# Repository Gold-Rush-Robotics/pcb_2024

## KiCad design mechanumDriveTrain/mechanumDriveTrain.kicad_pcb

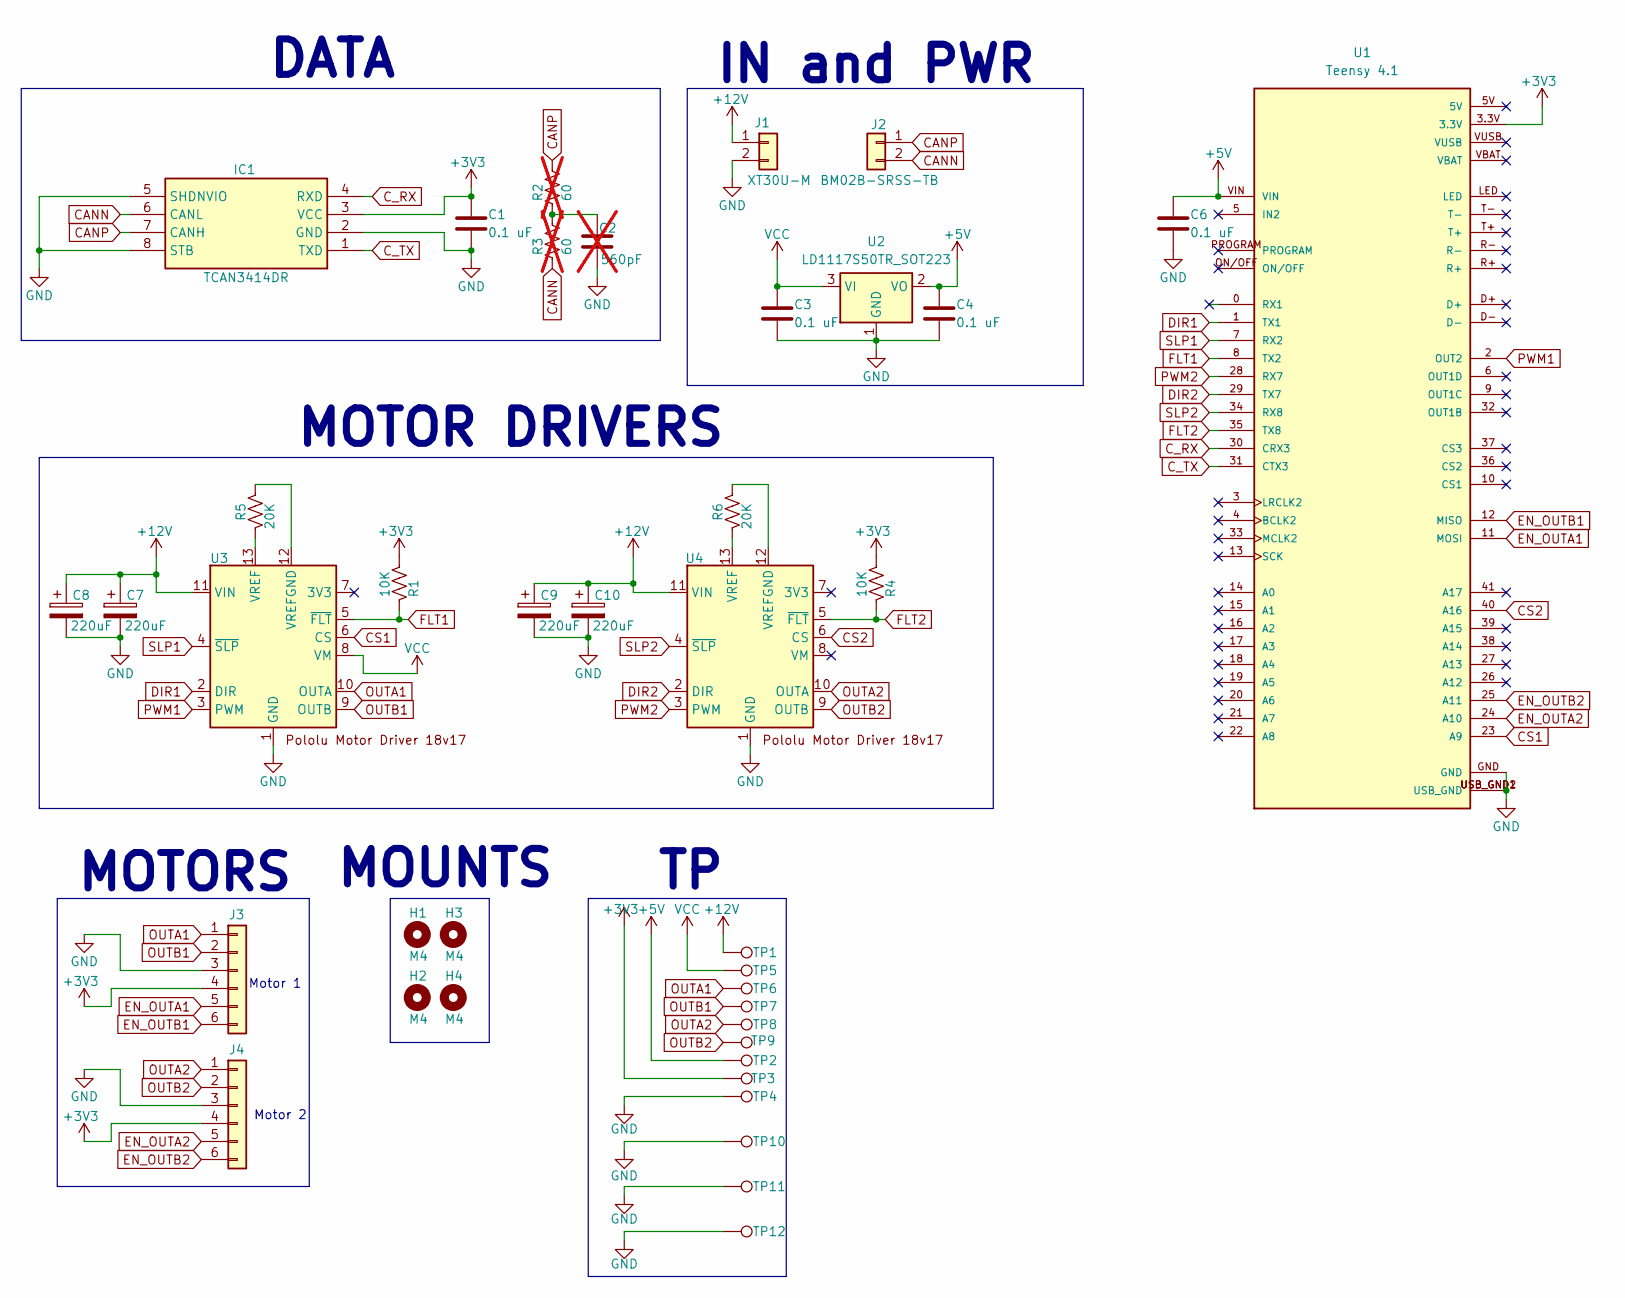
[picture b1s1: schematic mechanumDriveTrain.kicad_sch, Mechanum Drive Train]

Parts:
C1, C3, C4, C6: 0.1 uF; C_0805_2012Metric_Pad1.18x1.45mm_HandSolder
C2: 560pF; C_0805_2012Metric_Pad1.18x1.45mm_HandSolder; not fitted
C7, C8, C9, C10: 220uF; CP_Radial_D6.3mm_P2.50mm
H1, H2, H3, H4: M4; MountingHole_4.3mm_M4_DIN965
IC1: TCAN3414DR; SOIC-8_3.9x4.9mm_P1.27mm; Mouser Part Number 595-TCAN3414DR
J1: XT30U-M; AMASS_XT30U-M_1x02_P5.0mm_Vertical
J2: BM02B-SRSS-TB; JST_SH_BM02B-SRSS-TB_1x02-1MP_P1.00mm_Vertical
J3, J4: 5 pin dupont; PinHeader_1x06_P2.54mm_Vertical
R1, R4: 10K; R_0805_2012Metric_Pad1.20x1.40mm_HandSolder
R2, R3: 60; R_0805_2012Metric_Pad1.20x1.40mm_HandSolder; not fitted
R5, R6: 20K; R_Axial_DIN0207_L6.3mm_D2.5mm_P5.08mm_Vertical
TP1, TP2, TP3, TP4, TP5, TP6, TP7, TP8, TP9, TP10, TP11, TP12: TestPoint_Loop_D1.80mm_Drill1.0mm_Beaded
U1: Teensy 4.1; Teensy41; PARTREV 4.1
U2: LD1117S50TR_SOT223; SOT-223-3_TabPin2
U3, U4: Pololu_G2_Motor_Driver_18v17

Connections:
+3V3: C1.1, IC1.3 (VCC), J3.4, J4.4, R1.1, R4.1, TP3.1, U1.3.3V
+5V: C4.1, C6.1, TP2.1, U1.VIN, U2.2 (VO)
+12V: C7.1, C8.1, C9.1, C10.1, J1.1, TP1.1, U3.11 (VIN), U4.11 (VIN)
CANN: IC1.6 (CANL), J2.2, R3.2
CANP: IC1.7 (CANH), J2.1, R2.1
CS1: U1.23 (A9), U3.6 (CS)
CS2: U1.40 (A16), U4.6 (CS)
C_RX: IC1.4 (RXD), U1.30 (CRX3)
C_TX: IC1.1 (TXD), U1.31 (CTX3)
DIR1: U1.1 (TX1), U3.2 (DIR)
DIR2: U1.29 (TX7), U4.2 (DIR)
EN_OUTA1: J3.5, U1.11 (MOSI)
EN_OUTA2: J4.5, U1.24 (A10)
EN_OUTB1: J3.6, U1.12 (MISO)
EN_OUTB2: J4.6, U1.25 (A11)
FLT1: R1.2, U1.8 (TX2), U3.5 (~FLT)
FLT2: R4.2, U1.35 (TX8), U4.5 (~FLT)
GND: C1.2, C2.2, C3.2, C4.2, C6.2, C7.2, C8.2, C9.2, C10.2, IC1.2 (GND), IC1.5 (SHDNVIO), IC1.8 (STB), J1.2, J3.3, J4.3, TP4.1, TP10.1, TP11.1, TP12.1, U1.GND, U1.USB_GND1 (USB_GND), U1.USB_GND2 (USB_GND), U2.1 (GND), U3.1 (GND), U4.1 (GND)
unnamed: C2.1, R2.2, R3.1
unnamed: R5.1, U3.13 (VREF)
unnamed: R5.2, U3.12 (VREFGND)
unnamed: R6.1, U4.13 (VREF)
unnamed: R6.2, U4.12 (VREFGND)
OUTA1: J3.1, TP6.1, U3.10 (OUTA)
OUTA2: J4.1, TP8.1, U4.10 (OUTA)
OUTB1: J3.2, TP7.1, U3.9 (OUTB)
OUTB2: J4.2, TP9.1, U4.9 (OUTB)
PWM1: U1.2 (OUT2), U3.3 (PWM)
PWM2: U1.28 (RX7), U4.3 (PWM)
SLP1: U1.7 (RX2), U3.4 (~SLP)
SLP2: U1.34 (RX8), U4.4 (~SLP)
VCC: C3.1, TP5.1, U2.3 (VI), U3.8 (VM)

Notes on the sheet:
MOUNTS
Motor 1
DATA
IN and PWR
MOTOR DRIVERS
Motor 2
MOTORS

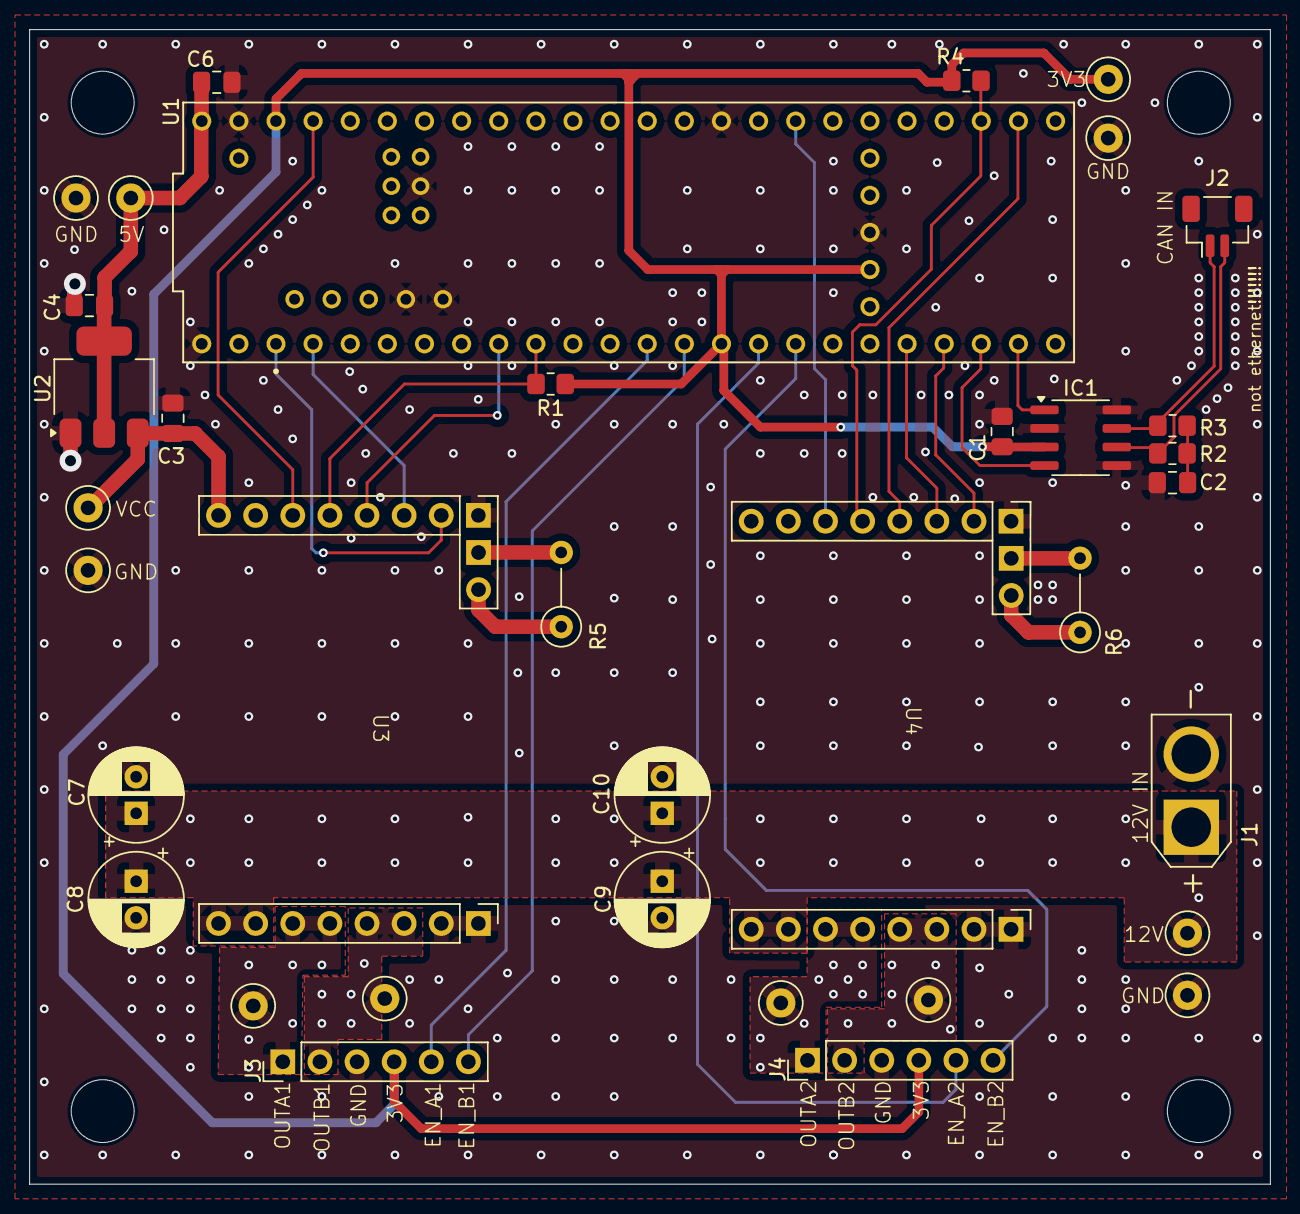
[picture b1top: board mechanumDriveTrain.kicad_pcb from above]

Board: 2 copper layers, 84.9 x 79.0 mm, 40 parts (0 on the bottom side), 32 nets.

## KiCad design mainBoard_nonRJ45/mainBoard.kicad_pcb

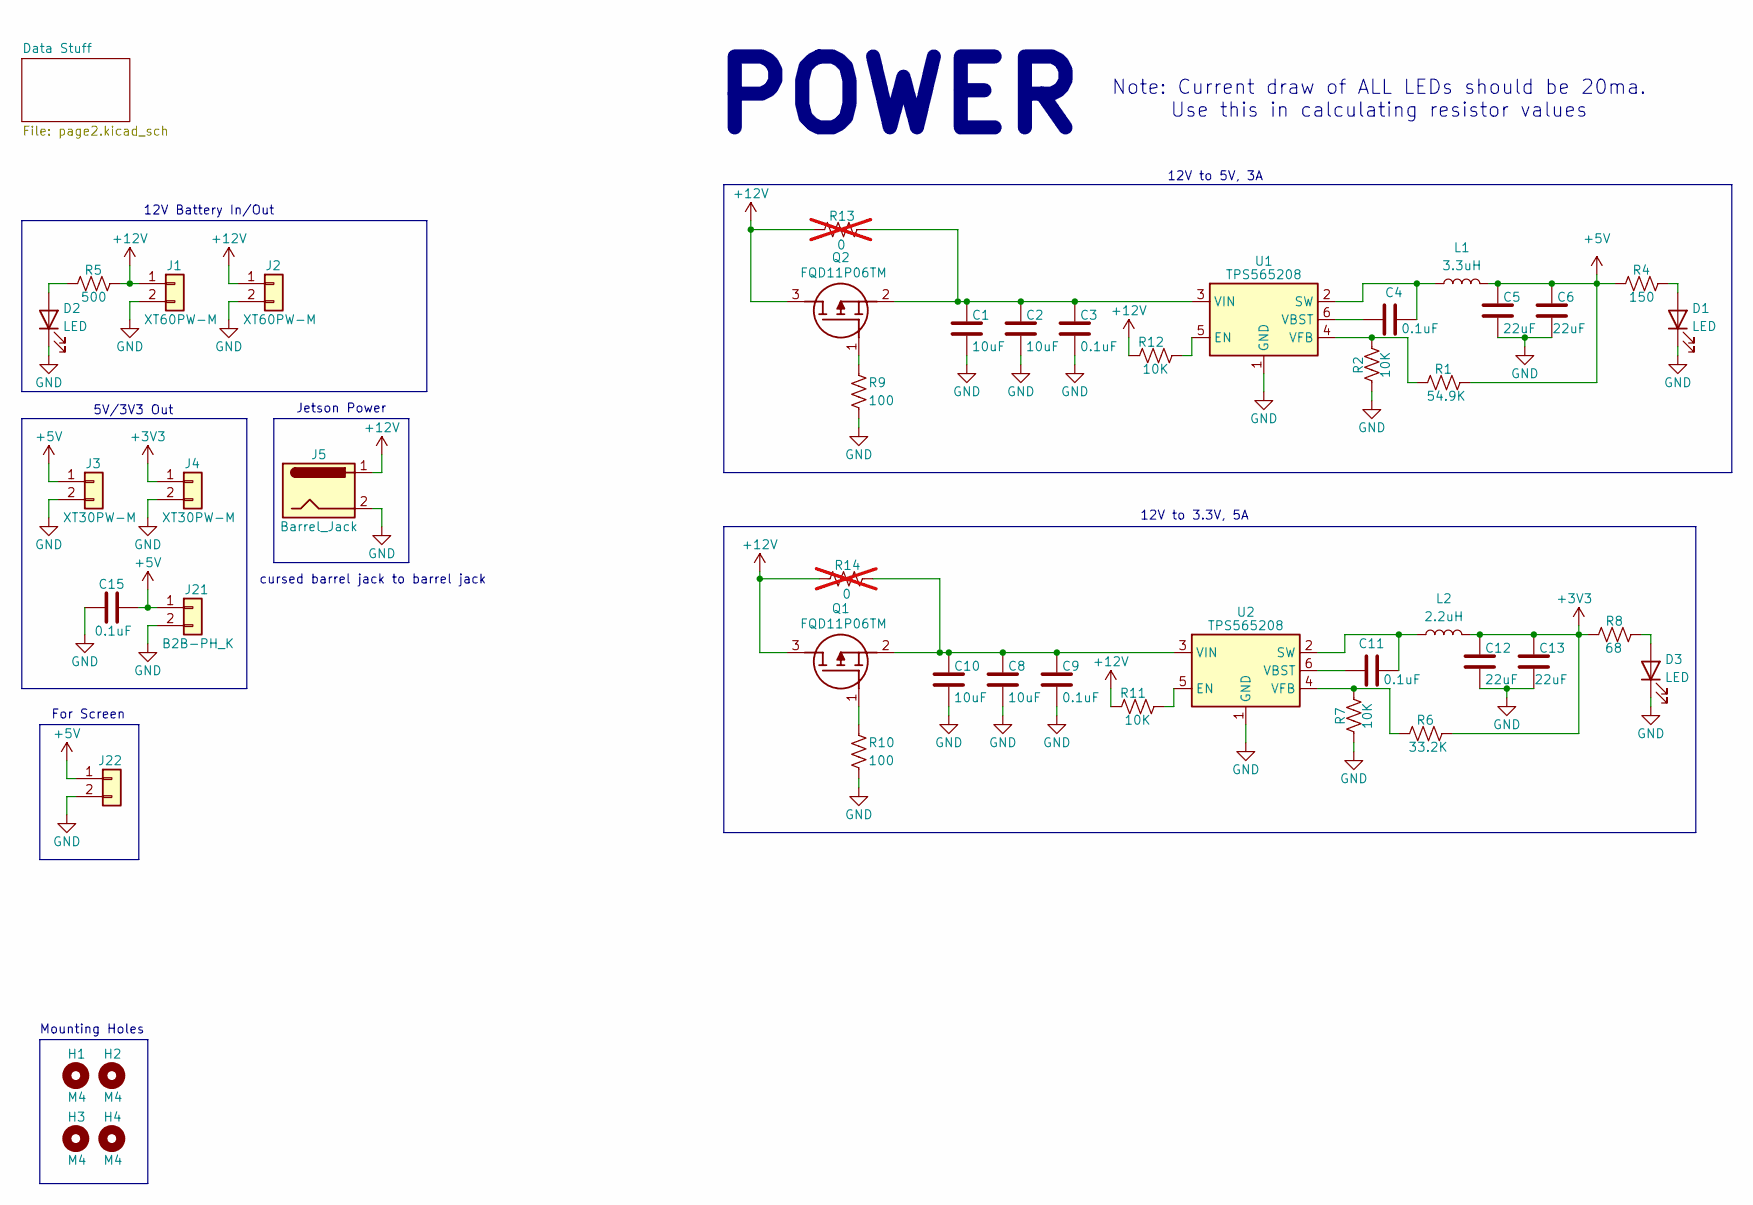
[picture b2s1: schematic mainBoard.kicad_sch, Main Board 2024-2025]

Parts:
C1, C2, C8, C10: 10uF; C_0805_2012Metric_Pad1.18x1.45mm_HandSolder
C3, C4, C9, C11, C15: 0.1uF; C_0805_2012Metric_Pad1.18x1.45mm_HandSolder
C5, C6, C12, C13: 22uF; C_0805_2012Metric_Pad1.18x1.45mm_HandSolder
D1, D2, D3: LED; D_0805_2012Metric_Pad1.15x1.40mm_HandSolder
H1, H2, H3, H4: M4; MountingHole_4.3mm_M4_DIN965
J1, J2: XT60PW-M; AMASS_XT60PW-M_1x02_P7.20mm_Horizontal
J3, J4: XT30PW-M; AMASS_XT30PW-M_1x02_P2.50mm_Horizontal
J5: Barrel_Jack; BarrelJack_Kycon_KLDX-0202-xC_Horizontal
J21: B2B-PH_K; JST_PH_B2B-PH-K_1x02_P2.00mm_Vertical
J22: Conn_01x02; PinHeader_1x02_P2.54mm_Vertical
L1: 3.3uH; L_Abracon_ASPI-0630LR
L2: 2.2uH; L_Abracon_ASPI-0630LR
Q1, Q2: FQD11P06TM; TO-252-2; Manufacturer_Part_Number FQD11P06TM; Mouser Part Number 512-FQD11P06TM
R1: 54.9K; R_0805_2012Metric_Pad1.20x1.40mm_HandSolder
R2, R7, R11, R12: 10K; R_0805_2012Metric_Pad1.20x1.40mm_HandSolder
R4: 150; R_0805_2012Metric_Pad1.20x1.40mm_HandSolder
R5: 500; R_0805_2012Metric_Pad1.20x1.40mm_HandSolder
R6: 33.2K; R_0805_2012Metric_Pad1.20x1.40mm_HandSolder
R8: 68; R_0805_2012Metric_Pad1.20x1.40mm_HandSolder
R9, R10: 100; R_0805_2012Metric_Pad1.20x1.40mm_HandSolder
R13, R14: 0; R_1210_3225Metric_Pad1.30x2.65mm_HandSolder; not fitted
U1, U2: TPS565208; SOT-23-6

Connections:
+3V3: C12.1, C13.1, J4.1, L2.2, R6.2, R8.1; also elsewhere on the board
+5V: C5.1, C6.1, C15.2, J3.1, J21.1, J22.1, L1.2, R1.2, R4.1
+12V: J1.1, J2.1, J5.1, Q1.3 (D), Q2.3 (D), R5.2, R11.1, R12.1, R13.2, R14.2; also elsewhere on the board
GND: C1.2, C2.2, C3.2, C5.2, C6.2, C8.2, C9.2, C10.2, C12.2, C13.2, C15.1, D1.1 (K), D2.1 (K), D3.1 (K), J1.2, J2.2, J3.2, J4.2, J5.2, J21.2, J22.2, R2.1, R7.1, R9.2, R10.2, U1.1 (GND), U2.1 (GND); also elsewhere on the board
unnamed: D1.2 (A), R4.2
unnamed: D2.2 (A), R5.1
unnamed: D3.2 (A), R8.2
unnamed: Q1.1 (G), R10.1
unnamed: C8.1, C9.1, C10.1, Q1.2 (S), R14.1, U2.3 (VIN)
unnamed: Q2.1 (G), R9.1
unnamed: C1.1, C2.1, C3.1, Q2.2 (S), R13.1, U1.3 (VIN)
unnamed: R12.2, U1.5 (EN)
unnamed: C4.2, L1.1, U1.2 (SW)
unnamed: C4.1, U1.6 (VBST)
unnamed: R1.1, R2.2, U1.4 (VFB)
unnamed: R11.2, U2.5 (EN)
unnamed: C11.2, L2.1, U2.2 (SW)
unnamed: C11.1, U2.6 (VBST)
unnamed: R6.1, R7.2, U2.4 (VFB)

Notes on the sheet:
12V Battery In/Out
12V to 5V, 3A
Mounting Holes
Jetson Power
For Screen
cursed barrel jack to barrel jack
5V/3V3 Out
12V to 3.3V, 5A
POWER
Note: Current draw of ALL LEDs should be 20ma. Use this in calculating resistor values

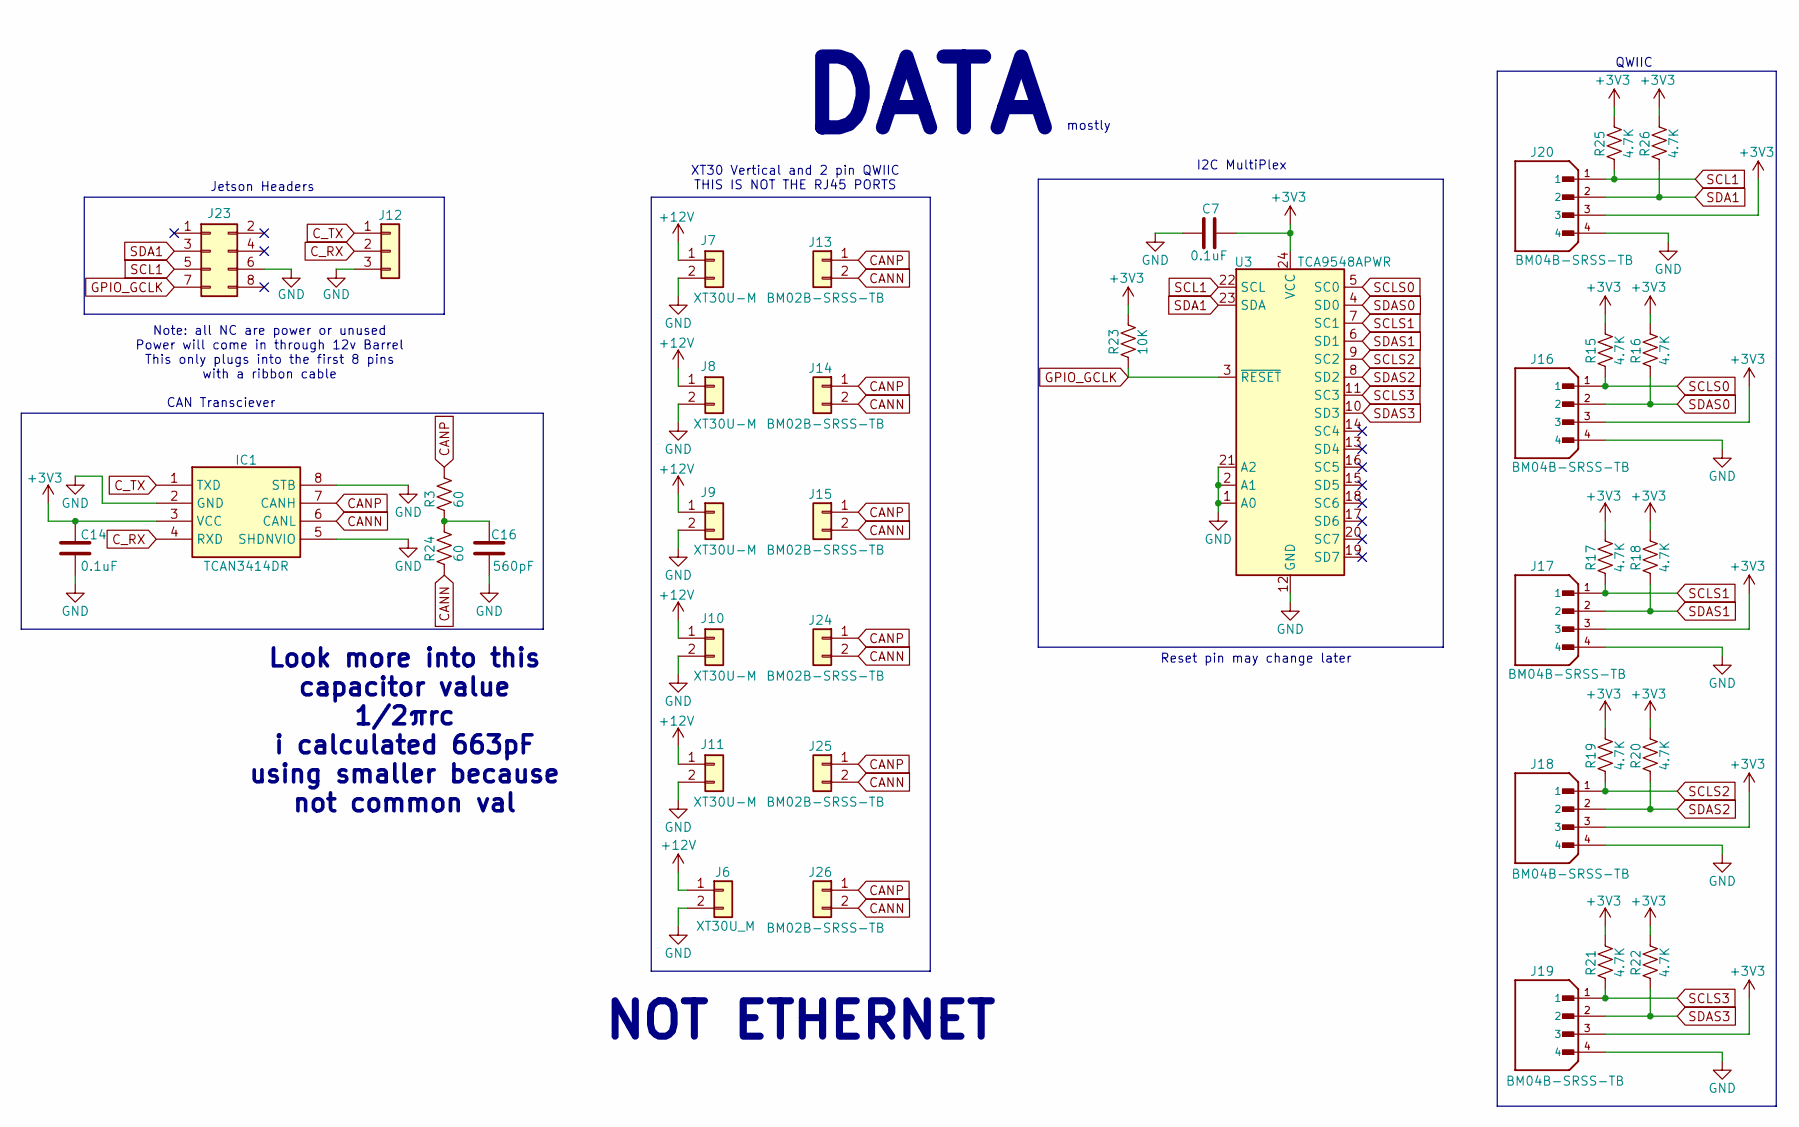
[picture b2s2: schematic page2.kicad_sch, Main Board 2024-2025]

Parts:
C7, C14: 0.1uF; C_0805_2012Metric_Pad1.18x1.45mm_HandSolder
C16: 560pF; C_0805_2012Metric_Pad1.18x1.45mm_HandSolder
IC1: TCAN3414DR; SOIC-8_3.9x4.9mm_P1.27mm; Mouser Part Number 595-TCAN3414DR
J6: XT30U_M; AMASS_XT30U-M_1x02_P5.0mm_Vertical
J7, J8, J9, J10, J11: XT30U-M; AMASS_XT30U-M_1x02_P5.0mm_Vertical
J12: Conn_01x03; PinHeader_1x03_P2.54mm_Vertical
J13, J14, J15, J24, J25, J26: BM02B-SRSS-TB; JST_SH_BM02B-SRSS-TB_1x02-1MP_P1.00mm_Vertical
J16, J17, J18, J19, J20: BM04B-SRSS-TB; JST_SH_BM04B-SRSS-TB_1x04-1MP_P1.00mm_Vertical; PARTREV NA
J23: Conn_02x04_Odd_Even; PinHeader_2x04_P2.54mm_Vertical
R3, R24: 60; R_0805_2012Metric_Pad1.20x1.40mm_HandSolder
R15, R16, R17, R18, R19, R20, R21, R22, R25, R26: 4.7K; R_0805_2012Metric_Pad1.20x1.40mm_HandSolder
R23: 10K; R_0805_2012Metric_Pad1.20x1.40mm_HandSolder
U3: TCA9548APWR; TSSOP-24_4.4x7.8mm_P0.65mm

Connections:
+3V3: C7.1, C14.1, IC1.3 (VCC), J16.3, J17.3, J18.3, J19.3, J20.3, R15.1, R16.1, R17.1, R18.1, R19.1, R20.1, R21.1, R22.1, R23.1, R25.1, R26.1, U3.24 (VCC); also elsewhere on the board
+12V: J6.1, J7.1, J8.1, J9.1, J10.1, J11.1; also elsewhere on the board
CANN: IC1.6 (CANL), J13.2, J14.2, J15.2, J24.2, J25.2, J26.2, R24.2
CANP: IC1.7 (CANH), J13.1, J14.1, J15.1, J24.1, J25.1, J26.1, R3.1
C_RX: IC1.4 (RXD), J12.2
C_TX: IC1.1 (TXD), J12.1
GND: C7.2, C14.2, C16.2, IC1.2 (GND), IC1.5 (SHDNVIO), IC1.8 (STB), J6.2, J7.2, J8.2, J9.2, J10.2, J11.2, J12.3, J16.4, J17.4, J18.4, J19.4, J20.4, J23.6, U3.1 (A0), U3.2 (A1), U3.12 (GND), U3.21 (A2); also elsewhere on the board
GPIO_GCLK: J23.7, R23.2, U3.3 (~RESET)
unnamed: C16.1, R3.2, R24.1
SCL1: J20.1, J23.5, R25.2, U3.22 (SCL)
SCLS0: J16.1, R15.2, U3.5 (SC0)
SCLS1: J17.1, R17.2, U3.7 (SC1)
SCLS2: J18.1, R19.2, U3.9 (SC2)
SCLS3: J19.1, R21.2, U3.11 (SC3)
SDA1: J20.2, J23.3, R26.2, U3.23 (SDA)
SDAS0: J16.2, R16.2, U3.4 (SD0)
SDAS1: J17.2, R18.2, U3.6 (SD1)
SDAS2: J18.2, R20.2, U3.8 (SD2)
SDAS3: J19.2, R22.2, U3.10 (SD3)

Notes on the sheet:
Look more into this capacitor value 1/2πrc i calculated 663pF using smaller because not common val
mostly
Note: all NC are power or unused Power will come in through 12v Barrel This only plugs into the first 8 pins with a ribbon cable
CAN Transciever
Jetson Headers
XT30 Vertical and 2 pin QWIIC THIS IS NOT THE RJ45 PORTS
DATA
I2C MultiPlex
NOT ETHERNET
QWIIC
Reset pin may change later

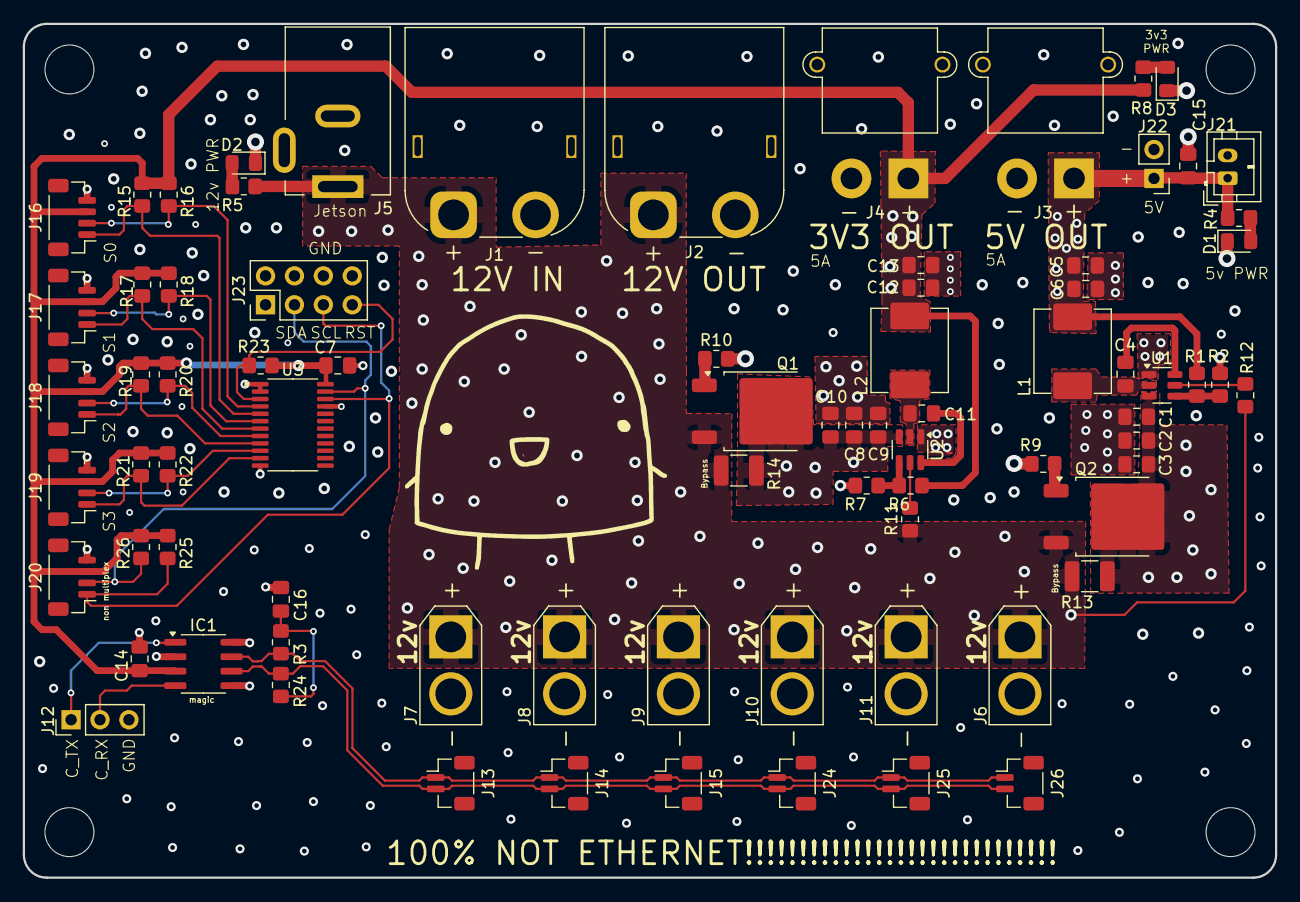
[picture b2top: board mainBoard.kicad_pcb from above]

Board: 4 copper layers, 110.0 x 75.0 mm, 83 parts (0 on the bottom side), 35 nets.

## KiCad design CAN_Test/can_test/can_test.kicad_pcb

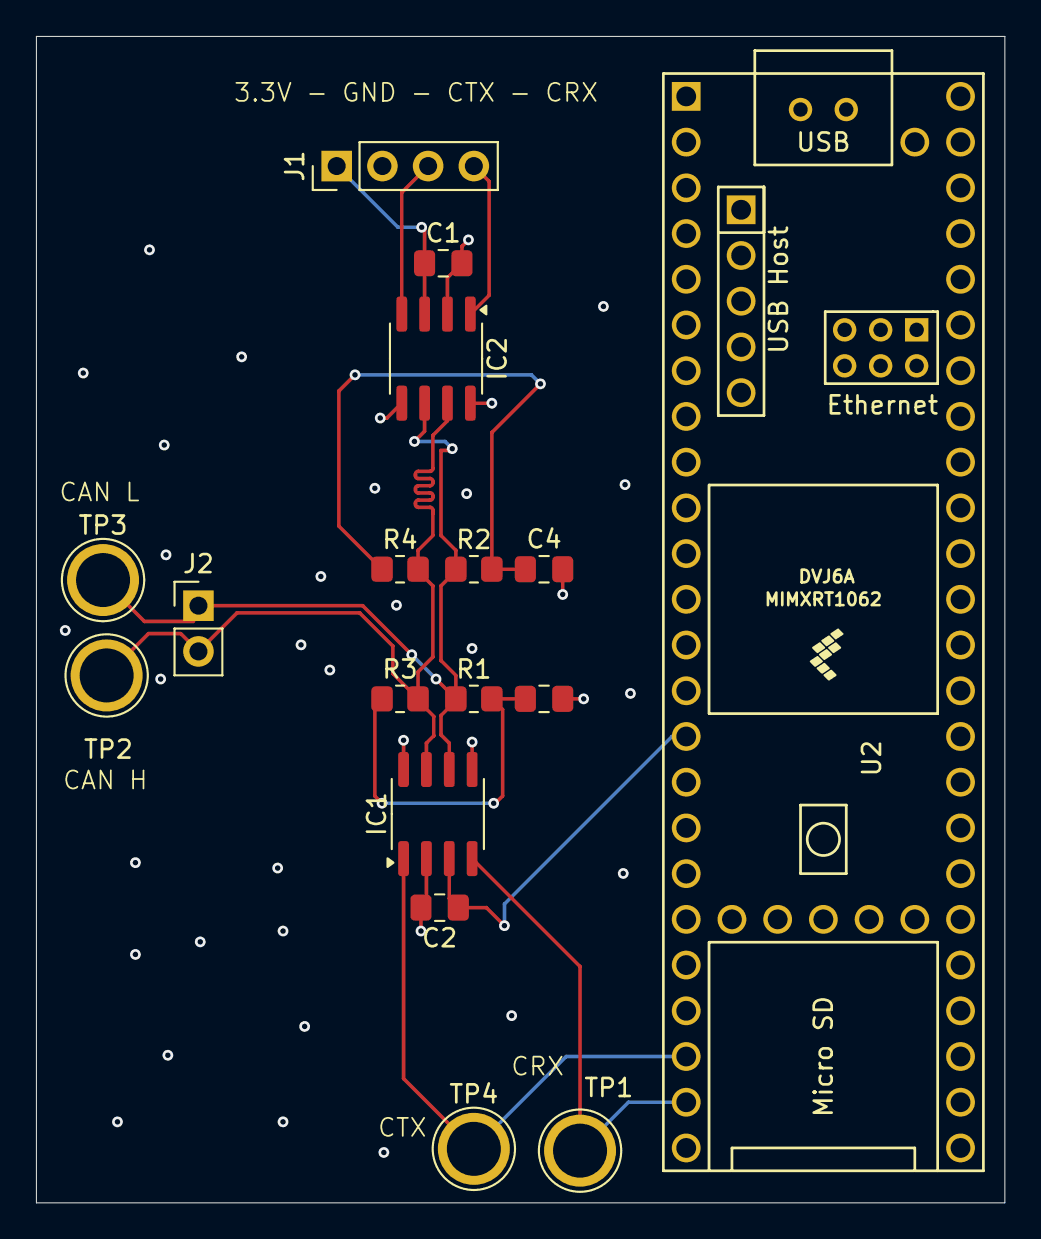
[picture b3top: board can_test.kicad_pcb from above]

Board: 4 copper layers, 53.8 x 64.8 mm, 17 parts (0 on the bottom side), 11 nets.

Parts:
C1, C2: 0.1 uF; C_0805_2012Metric_Pad1.18x1.45mm_HandSolder
C3, C4: C; C_0805_2012Metric_Pad1.18x1.45mm_HandSolder
IC1, IC2: TCAN3414DR; SOIC-8_3.9x4.9mm_P1.27mm
J1: Conn_01x04_Pin; PinHeader_1x04_P2.54mm_Vertical
J2: Conn_01x02_Pin; PinHeader_1x02_P2.54mm_Vertical
R1, R2, R3, R4: 60; R_0805_2012Metric_Pad1.20x1.40mm_HandSolder
TP1, TP2, TP3, TP4: TestPoint_Probe; TestPoint_Plated_Hole_D3.0mm
U2: Teensy4.1; Teensy41

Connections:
+3.3V: C2.1, IC1.3 (VCC), U2.15 (3V3)
CANN: IC1.6 (CANL), IC2.6 (CANL), J2.1, R1.1, R2.1, TP3.1
CANP: IC1.7 (CANH), IC2.7 (CANH), J2.2, R3.2, R4.2, TP2.1
CRX1: IC1.4 (RXD), TP1.1, U2.23 (31_CTX3)
CRX2: IC2.4 (RXD), J1.3
CTX1: IC1.1 (TXD), TP4.1, U2.22 (30_CRX3)
CTX2: IC2.1 (TXD), J1.4
GND: C1.2, C2.2, C3.2, C4.2, IC1.2 (GND), IC1.5 (SHDNVIO), IC1.8 (STB), IC2.2 (GND), IC2.5 (SHDNVIO), IC2.8 (STB), J1.2, U2.1 (GND), U2.47 (GND)
unnamed: C3.1, R1.2, R3.1
unnamed: C4.1, R2.2, R4.1
unnamed: C1.1, IC2.3 (VCC), J1.1

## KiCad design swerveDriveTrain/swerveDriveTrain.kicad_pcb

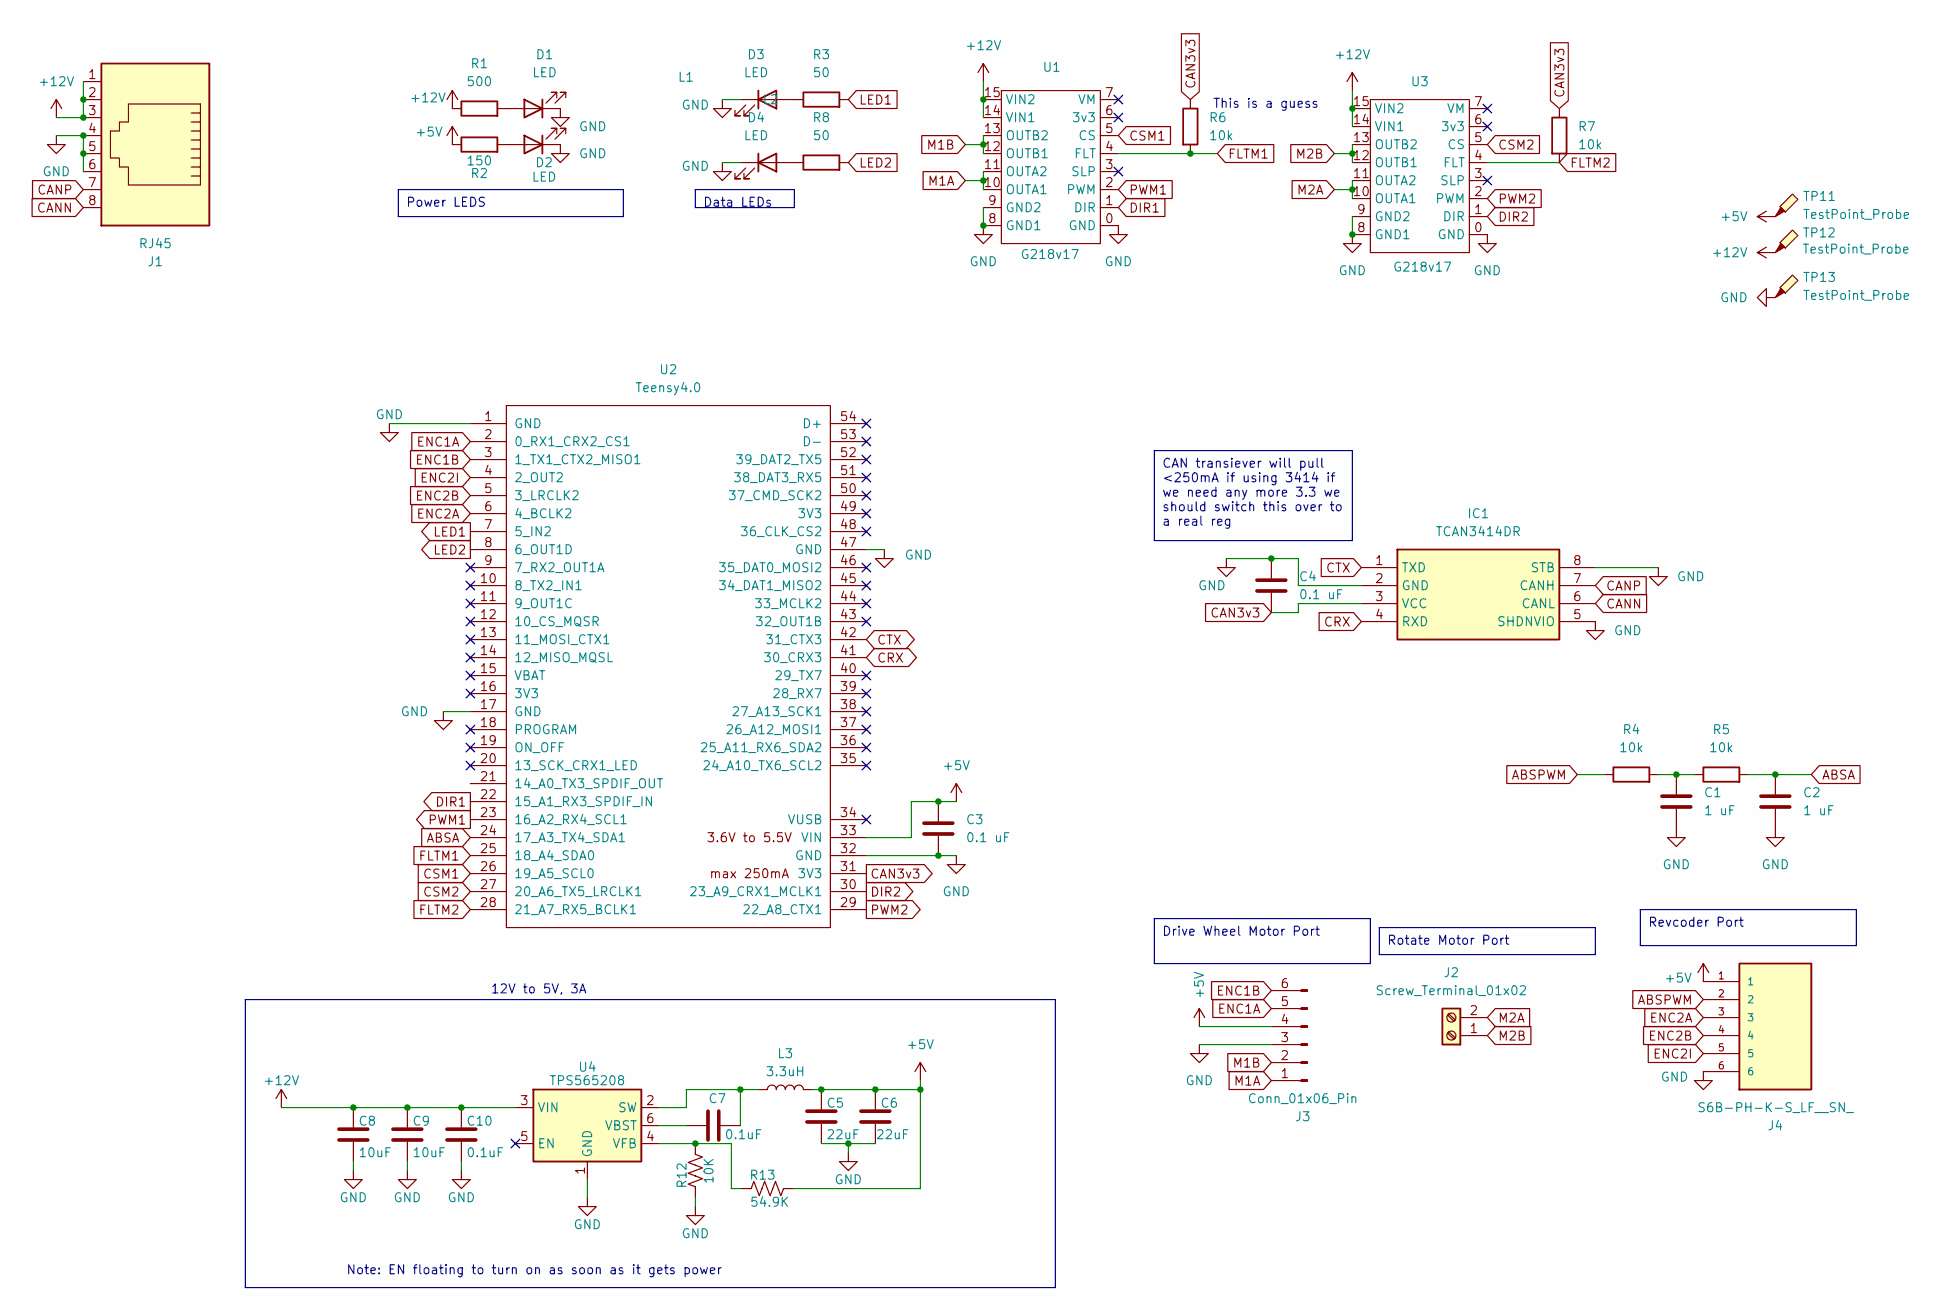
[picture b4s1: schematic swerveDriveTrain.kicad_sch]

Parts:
C1, C2: 1 uF; C_0805_2012Metric_Pad1.18x1.45mm_HandSolder
C3, C4: 0.1 uF; C_0805_2012Metric_Pad1.18x1.45mm_HandSolder
C5, C6: 22uF; C_0805_2012Metric_Pad1.18x1.45mm_HandSolder
C7, C10: 0.1uF; C_0805_2012Metric_Pad1.18x1.45mm_HandSolder
C8, C9: 10uF; C_0805_2012Metric_Pad1.18x1.45mm_HandSolder
D1, D2, D3, D4: LED; LED_0805_2012Metric_Pad1.15x1.40mm_HandSolder
IC1: TCAN3414DR; SOIC127P600X175-8N; Mouser Part Number 595-TCAN3414DR
J1: RJ45; RJ45_OST_PJ012-8P8CX_Vertical
J2: Screw_Terminal_01x02; PHOENIX_1935161
J3: Conn_01x06_Pin; PinHeader_1x06_P2.54mm_Horizontal
J4: S6B-PH-K-S_LF__SN_; JST_S6B-PH-K-S_LF__SN_; PARTREV N/A
L1: Logo_Small
L2: bird
L3: 3.3uH; L_Abracon_ASPI-0630LR
R1: 500; R_0805_2012Metric_Pad1.20x1.40mm_HandSolder
R2: 150; R_0805_2012Metric_Pad1.20x1.40mm_HandSolder
R3, R8: 50; R_0805_2012Metric_Pad1.20x1.40mm_HandSolder
R4, R5, R6, R7: 10k; R_0805_2012Metric_Pad1.20x1.40mm_HandSolder
R12: 10K; R_0805_2012Metric_Pad1.20x1.40mm_HandSolder
R13: 54.9K; R_0805_2012Metric_Pad1.20x1.40mm_HandSolder
TP11, TP12, TP13: TestPoint_Probe; TestPoint_Pad_D1.5mm
U1, U3: G218v17
U2: Teensy4.0; Teensy40_SMT
U4: TPS565208; SOT-23-6

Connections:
+5V: C3.1, C5.1, C6.1, J3.4, J4.1, L3.2, R2.1, R13.2, TP11.1, U2.33 (VIN)
+12V: C8.1, C9.1, C10.1, J1.1, J1.2, J1.3, R1.1, TP12.1, U1.14 (VIN1), U1.15 (VIN2), U3.14 (VIN1), U3.15 (VIN2), U4.3 (VIN)
ABSA: C2.1, R5.2, U2.24 (17_A3_TX4_SDA1)
ABSPWM: J4.2, R4.1
CAN3v3: C4.2, IC1.3 (VCC), R6.1, R7.1, U2.31 (3V3)
CANN: IC1.6 (CANL), J1.8
CANP: IC1.7 (CANH), J1.7
CRX: IC1.4 (RXD), U2.41 (30_CRX3)
CSM1: U1.5 (CS), U2.26 (19_A5_SCL0)
CSM2: U2.27 (20_A6_TX5_LRCLK1), U3.5 (CS)
CTX: IC1.1 (TXD), U2.42 (31_CTX3)
DIR1: U1.1 (DIR), U2.22 (15_A1_RX3_SPDIF_IN)
DIR2: U2.30 (23_A9_CRX1_MCLK1), U3.1 (DIR)
ENC1A: J3.5, U2.2 (0_RX1_CRX2_CS1)
ENC1B: J3.6, U2.3 (1_TX1_CTX2_MISO1)
ENC2A: J4.3, U2.6 (4_BCLK2)
ENC2B: J4.4, U2.5 (3_LRCLK2)
ENC2I: J4.5, U2.4 (2_OUT2)
FLTM1: R6.2, U1.4 (FLT), U2.25 (18_A4_SDA0)
FLTM2: R7.2, U2.28 (21_A7_RX5_BCLK1), U3.4 (FLT)
GND: C1.1, C2.2, C3.2, C4.1, C5.2, C6.2, C8.2, C9.2, C10.2, D1.1 (K), D2.1 (K), D3.1 (K), D4.1 (K), IC1.2 (GND), IC1.5 (SHDNVIO), IC1.8 (STB), J1.4, J1.5, J1.6, J3.3, J4.6, R12.1, TP13.1, U1.0 (GND), U1.8 (GND1), U1.9 (GND2), U2.1 (GND), U2.17 (GND), U2.32 (GND), U2.47 (GND), U3.0 (GND), U3.8 (GND1), U3.9 (GND2), U4.1 (GND)
LED1: R3.2, U2.7 (5_IN2)
LED2: R8.2, U2.8 (6_OUT1D)
M1A: J3.1, U1.10 (OUTA1), U1.11 (OUTA2)
M1B: J3.2, U1.12 (OUTB1), U1.13 (OUTB2)
M2A: J2.2, U3.10 (OUTA1), U3.11 (OUTA2)
M2B: J2.1, U3.12 (OUTB1), U3.13 (OUTB2)
unnamed: C1.2, R4.2, R5.1
unnamed: D1.2 (A), R1.2
unnamed: D2.2 (A), R2.2
unnamed: D3.2 (A), R3.1
unnamed: D4.2 (A), R8.1
unnamed: C7.2, L3.1, U4.2 (SW)
unnamed: C7.1, U4.6 (VBST)
unnamed: R12.2, R13.1, U4.4 (VFB)
PWM1: U1.2 (PWM), U2.23 (16_A2_RX4_SCL1)
PWM2: U2.29 (22_A8_CTX1), U3.2 (PWM)

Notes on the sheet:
Power LEDS
Data LEDs
CAN transiever will pull <250mA if using 3414 if we need any more 3.3 we should switch this over to a real reg
Drive Wheel Motor Port
Rotate Motor Port
Revcoder Port
This is a guess
12V to 5V, 3A
Note: EN floating to turn on as soon as it gets power

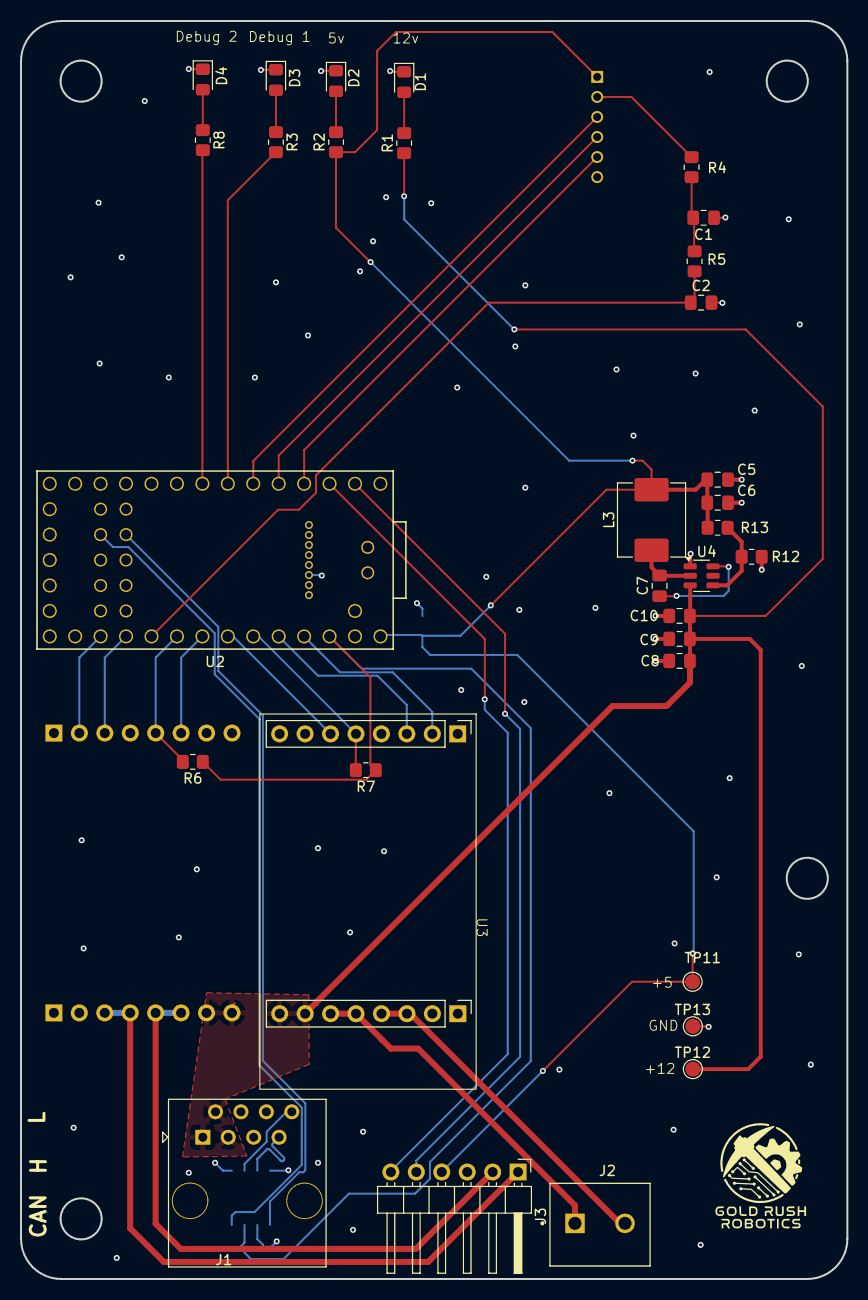
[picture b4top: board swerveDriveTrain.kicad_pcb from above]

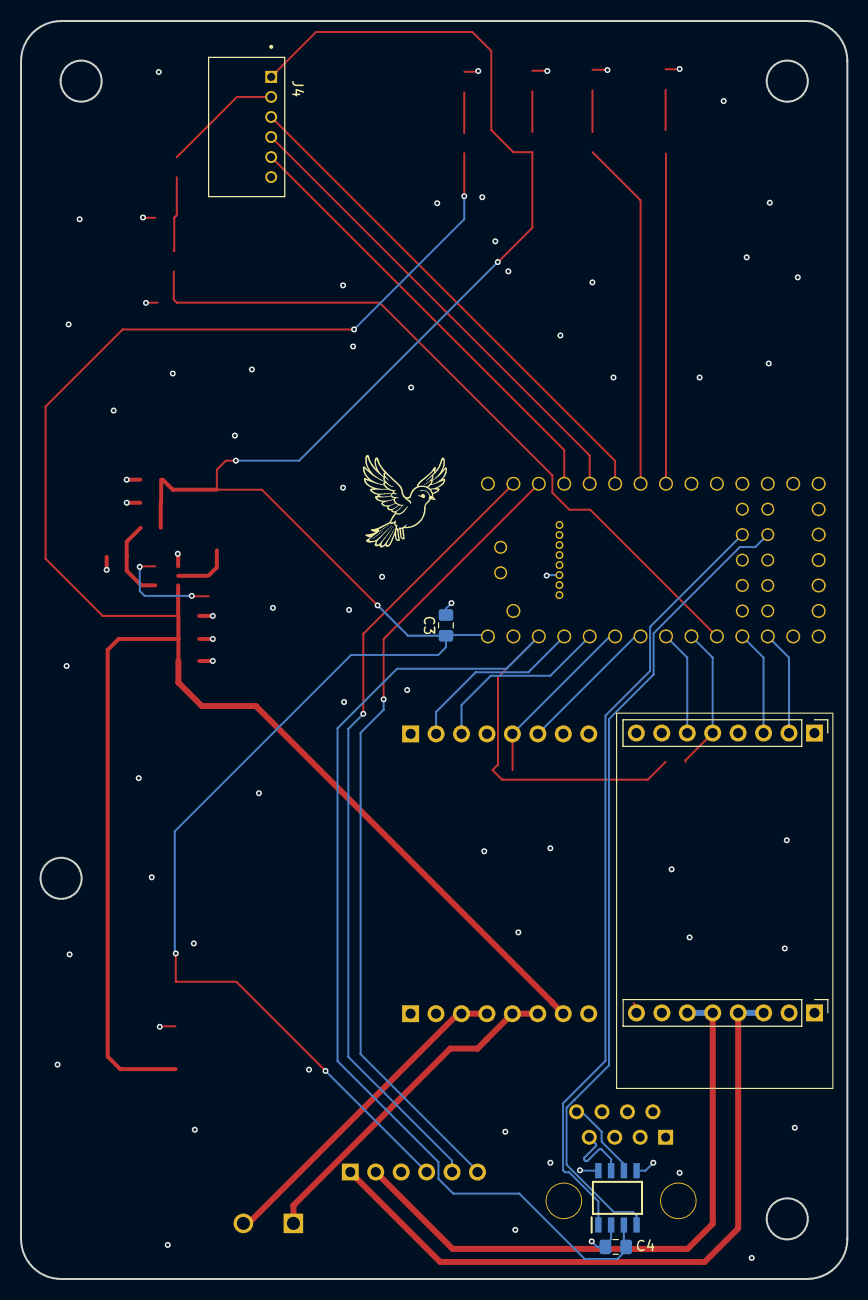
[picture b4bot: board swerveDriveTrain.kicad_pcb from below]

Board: 4 copper layers, 82.5 x 125.6 mm, 39 parts (6 on the bottom side), 37 nets.
